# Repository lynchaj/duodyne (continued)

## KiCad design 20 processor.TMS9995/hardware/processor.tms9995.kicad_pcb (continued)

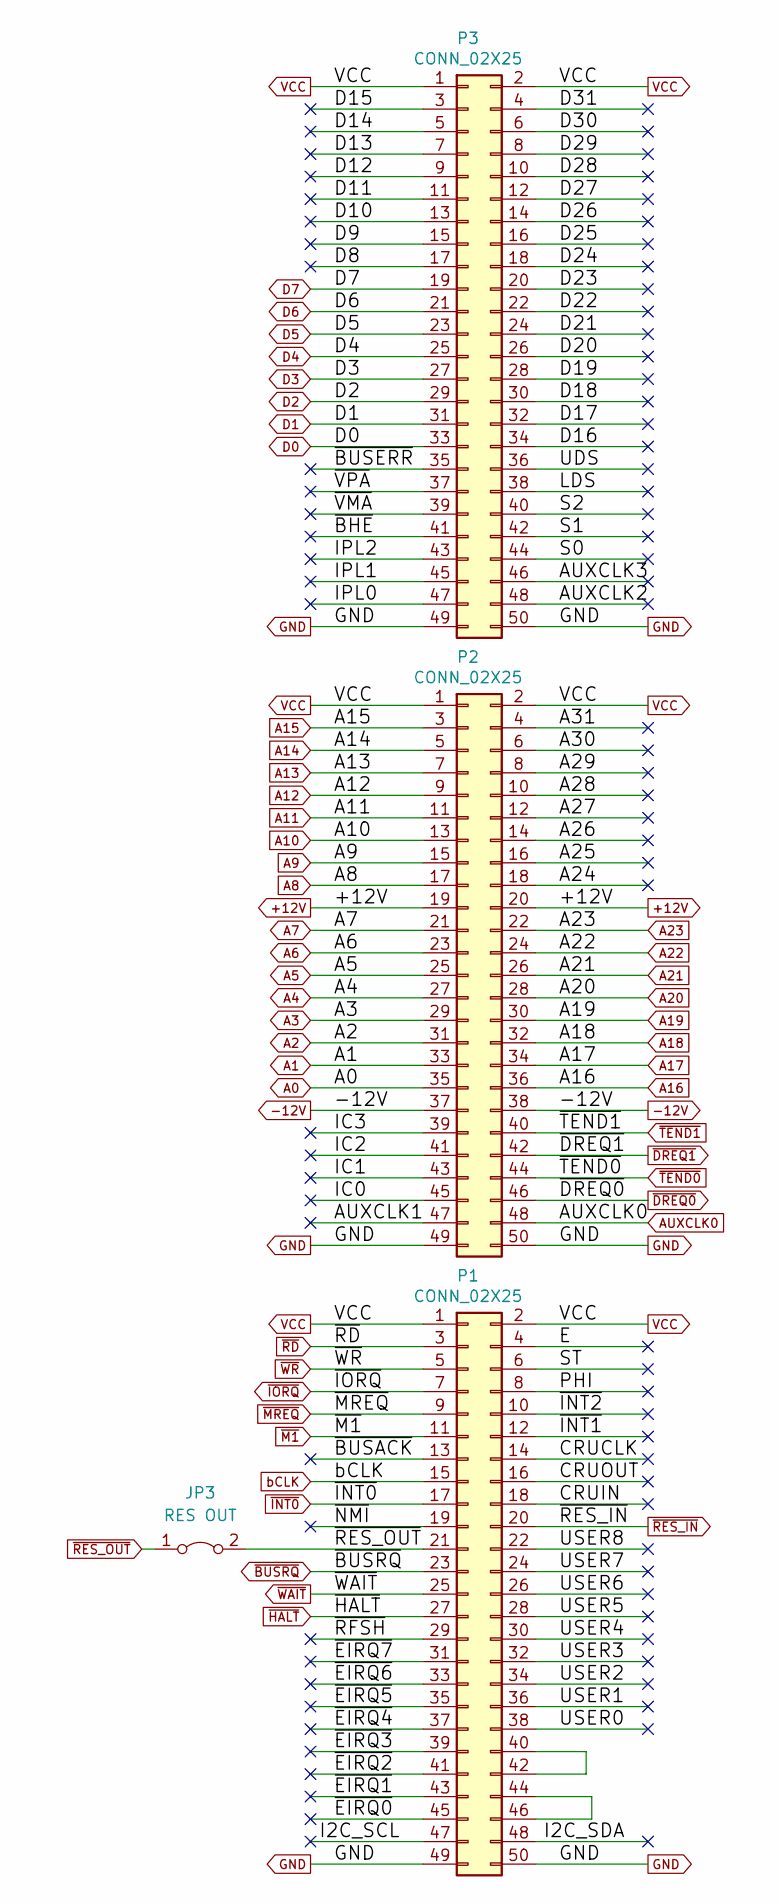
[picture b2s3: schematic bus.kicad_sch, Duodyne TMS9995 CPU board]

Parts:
JP3: RES OUT; SolderJumper-2_P1.3mm_Bridged_Pad1.0x1.5mm
P1, P2, P3: CONN_02X25; IDC-Header_2x25_P2.54mm_Horizontal

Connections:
+12V: P2.19, P2.20
-12V: P2.37, P2.38
/bus/A24: P2.18
/bus/A25: P2.16
/bus/A26: P2.14
/bus/A27: P2.12
/bus/A28: P2.10
/bus/A29: P2.8
/bus/A30: P2.6
/bus/A31: P2.4
/bus/AUXCLK1: P2.47
/bus/AUXCLK2: P3.48
/bus/AUXCLK3: P3.46
/bus/CRUCLK: P1.14
/bus/CRUIN: P1.18
/bus/CRUOUT: P1.16
/bus/D8: P3.17
/bus/D9: P3.15
/bus/D10: P3.13
/bus/D11: P3.11
/bus/D12: P3.9
/bus/D13: P3.7
/bus/D14: P3.5
/bus/D15: P3.3
/bus/D16: P3.34
/bus/D17: P3.32
/bus/D18: P3.30
/bus/D19: P3.28
/bus/D20: P3.26
/bus/D21: P3.24
/bus/D22: P3.22
/bus/D23: P3.20
/bus/D24: P3.18
/bus/D25: P3.16
/bus/D26: P3.14
/bus/D27: P3.12
/bus/D28: P3.10
/bus/D29: P3.8
/bus/D30: P3.6
/bus/D31: P3.4
/bus/E: P1.4
/bus/I2C_SCL: P1.47
/bus/I2C_SDA: P1.48
/bus/IC0: P2.45
/bus/IC1: P2.43
/bus/IC2: P2.41
/bus/IC3: P2.39
/bus/IPL0: P3.47
/bus/IPL1: P3.45
/bus/IPL2: P3.43
/bus/LDS: P3.38
/bus/PHI: P1.8
/bus/S0: P3.44
/bus/S1: P3.42
/bus/S2: P3.40
/bus/ST: P1.6
/bus/UDS: P3.36
/bus/USER0: P1.38
/bus/USER1: P1.36
/bus/USER2: P1.34
/bus/USER3: P1.32
/bus/USER4: P1.30
/bus/USER5: P1.28
/bus/USER6: P1.26
/bus/USER7: P1.24
/bus/USER8: P1.22
/bus/~BHE: P3.41
/bus/~BUSACK: P1.13
/bus/~BUSERR: P3.35
/bus/~EIRQ0: P1.45
/bus/~EIRQ1: P1.43
/bus/~EIRQ2: P1.41
/bus/~EIRQ3: P1.39
/bus/~EIRQ4: P1.37
/bus/~EIRQ5: P1.35
/bus/~EIRQ6: P1.33
/bus/~EIRQ7: P1.31
/bus/~INT1: P1.12
/bus/~INT2: P1.10
/bus/~NMI: P1.19
/bus/~RFSH: P1.29
/bus/~VMA: P3.39
/bus/~VPA: P3.37
A0: P2.35; also elsewhere on the board
A1: P2.33; also elsewhere on the board
A2: P2.31; also elsewhere on the board
A3: P2.29; also elsewhere on the board
A4: P2.27; also elsewhere on the board
A5: P2.25; also elsewhere on the board
A6: P2.23; also elsewhere on the board
A7: P2.21; also elsewhere on the board
A8: P2.17; also elsewhere on the board
A9: P2.15; also elsewhere on the board
A10: P2.13; also elsewhere on the board
A11: P2.11; also elsewhere on the board
A12: P2.9; also elsewhere on the board
A13: P2.7; also elsewhere on the board
A14: P2.5; also elsewhere on the board
A15: P2.3; also elsewhere on the board
A16: P2.36; also elsewhere on the board
A17: P2.34; also elsewhere on the board
A18: P2.32; also elsewhere on the board
A19: P2.30; also elsewhere on the board
A20: P2.28; also elsewhere on the board
A21: P2.26; also elsewhere on the board
A22: P2.24; also elsewhere on the board
A23: P2.22; also elsewhere on the board
AUXCLK0: P2.48; also elsewhere on the board
D0: P3.33; also elsewhere on the board
D1: P3.31; also elsewhere on the board
D2: P3.29; also elsewhere on the board
D3: P3.27; also elsewhere on the board
D4: P3.25; also elsewhere on the board
D5: P3.23; also elsewhere on the board
D6: P3.21; also elsewhere on the board
D7: P3.19; also elsewhere on the board
GND: P1.49, P1.50, P2.49, P2.50, P3.49, P3.50; also elsewhere on the board
unnamed: P1.40, P1.42
unnamed: P1.44, P1.46
VCC: P1.1, P1.2, P2.1, P2.2, P3.1, P3.2; also elsewhere on the board
bCLK: P1.15; also elsewhere on the board
~BUSRQ: P1.23; also elsewhere on the board
~DREQ0: P2.46; also elsewhere on the board
~DREQ1: P2.42; also elsewhere on the board
~HALT: P1.27; also elsewhere on the board
~INT0: P1.17; also elsewhere on the board
~IORQ: P1.7; also elsewhere on the board
~M1: P1.11; also elsewhere on the board
~MREQ: P1.9; also elsewhere on the board
~RD: P1.3; also elsewhere on the board
~RES_IN: P1.20; also elsewhere on the board
~TEND0: P2.44; also elsewhere on the board
~TEND1: P2.40; also elsewhere on the board
~WAIT: P1.25; also elsewhere on the board
~WR: P1.5; also elsewhere on the board

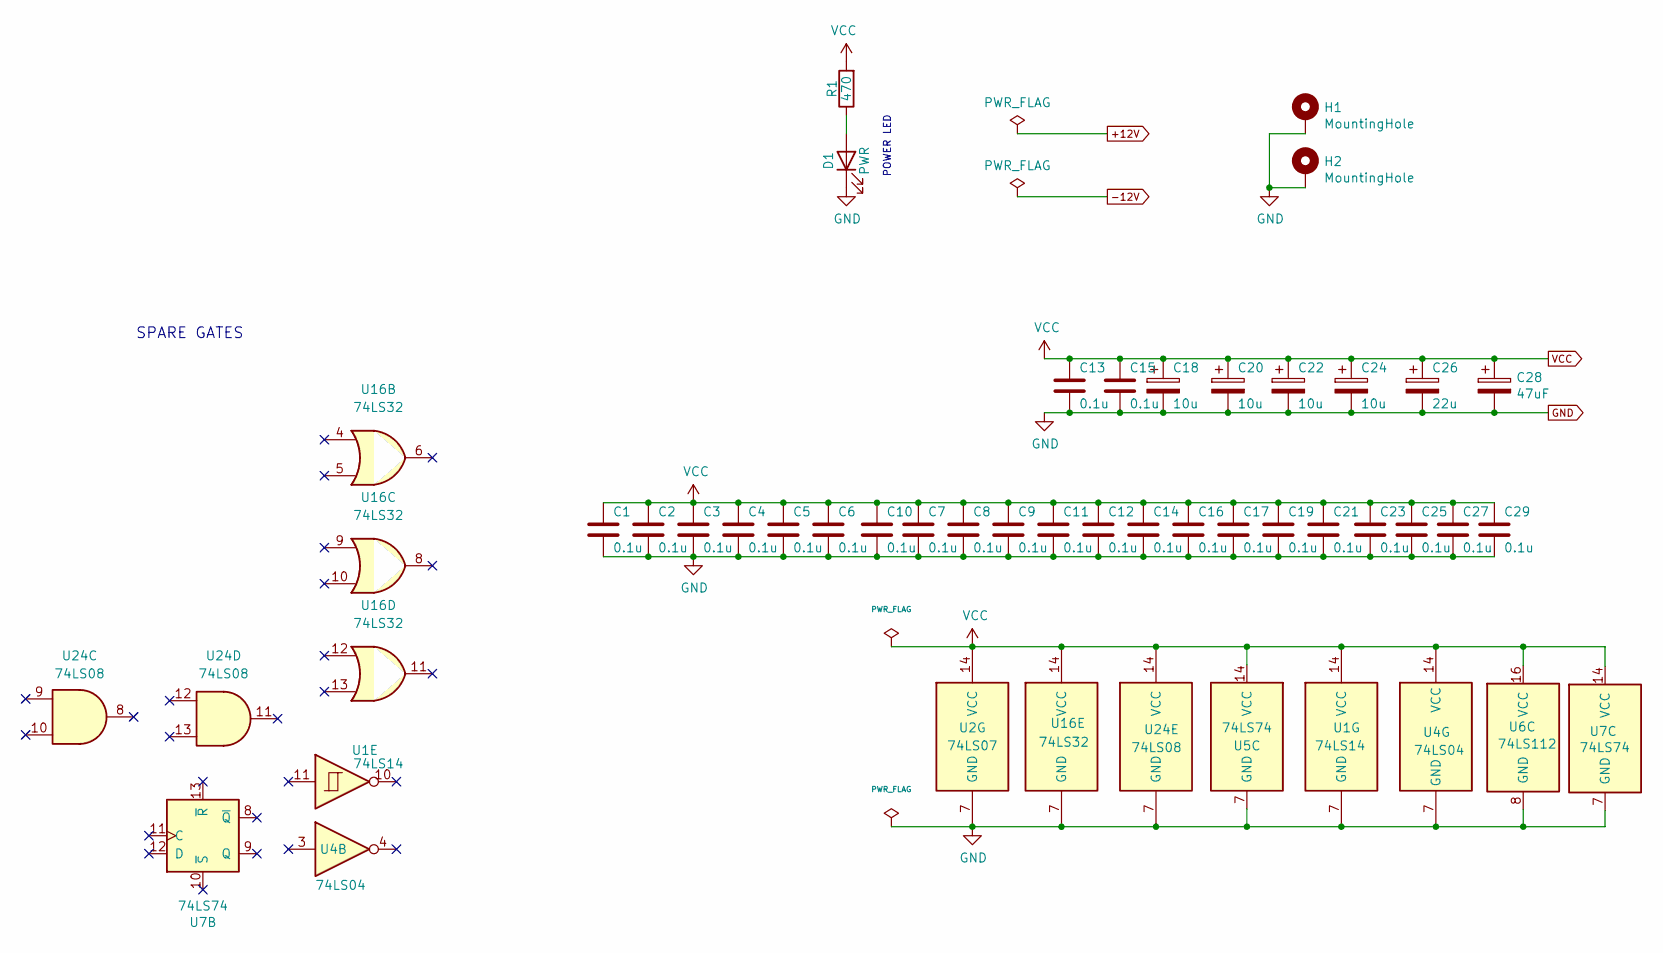
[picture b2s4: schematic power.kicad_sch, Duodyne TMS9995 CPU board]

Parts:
C1, C2, C3, C4, C5, C6, C7, C8, C9, C10, C11, C12, C13, C14, C15, C16, C17, C19, C21, C23, C25, C27, C29: 0.1u; C_Disc_D5.0mm_W2.5mm_P5.00mm
C18, C20, C22, C24: 10u; CP_Radial_D5.0mm_P2.50mm
C26: 22u; CP_Radial_D5.0mm_P2.50mm
C28: 47uF; CP_Radial_D5.0mm_P2.50mm
D1: PWR; LED_D3.0mm_Horizontal_O3.81mm_Z2.0mm
H1, H2: MountingHole; MountingHole_3.2mm_M3_Pad
R1: 470; R_Axial_DIN0207_L6.3mm_D2.5mm_P7.62mm_Horizontal
U1: 74LS14; DIP-14_W7.62mm_Socket_LongPads
U2: 74LS07; DIP-14_W7.62mm_Socket_LongPads
U4: 74LS04; DIP-14_W7.62mm_Socket_LongPads
U5, U7: 74LS74; DIP-14_W7.62mm_Socket_LongPads
U6: 74LS112; DIP-16_W7.62mm_Socket_LongPads
U16: 74LS32; DIP-14_W7.62mm_Socket_LongPads
U24: 74LS08; DIP-14_W7.62mm_Socket_LongPads

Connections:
GND: C1.2, C2.2, C3.2, C4.2, C5.2, C6.2, C7.2, C8.2, C9.2, C10.2, C11.2, C12.2, C13.2, C14.2, C15.2, C16.2, C17.2, C18.2, C19.2, C20.2, C21.2, C22.2, C23.2, C24.2, C25.2, C26.2, C27.2, C28.2, C29.2, D1.1 (K), H1.1, H2.1, U1.7 (GND), U2.7 (GND), U4.7 (GND), U5.7 (GND), U6.8 (GND), U7.7 (GND), U16.7 (GND), U24.7 (GND); also elsewhere on the board
unnamed: D1.2 (A), R1.1
VCC: C1.1, C2.1, C3.1, C4.1, C5.1, C6.1, C7.1, C8.1, C9.1, C10.1, C11.1, C12.1, C13.1, C14.1, C15.1, C16.1, C17.1, C18.1, C19.1, C20.1, C21.1, C22.1, C23.1, C24.1, C25.1, C26.1, C27.1, C28.1, C29.1, R1.2, U1.14 (VCC), U2.14 (VCC), U4.14 (VCC), U5.14 (VCC), U6.16 (VCC), U7.13 (~R), U7.14 (VCC), U16.14 (VCC), U24.14 (VCC); also elsewhere on the board

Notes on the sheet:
POWER LED
SPARE GATES

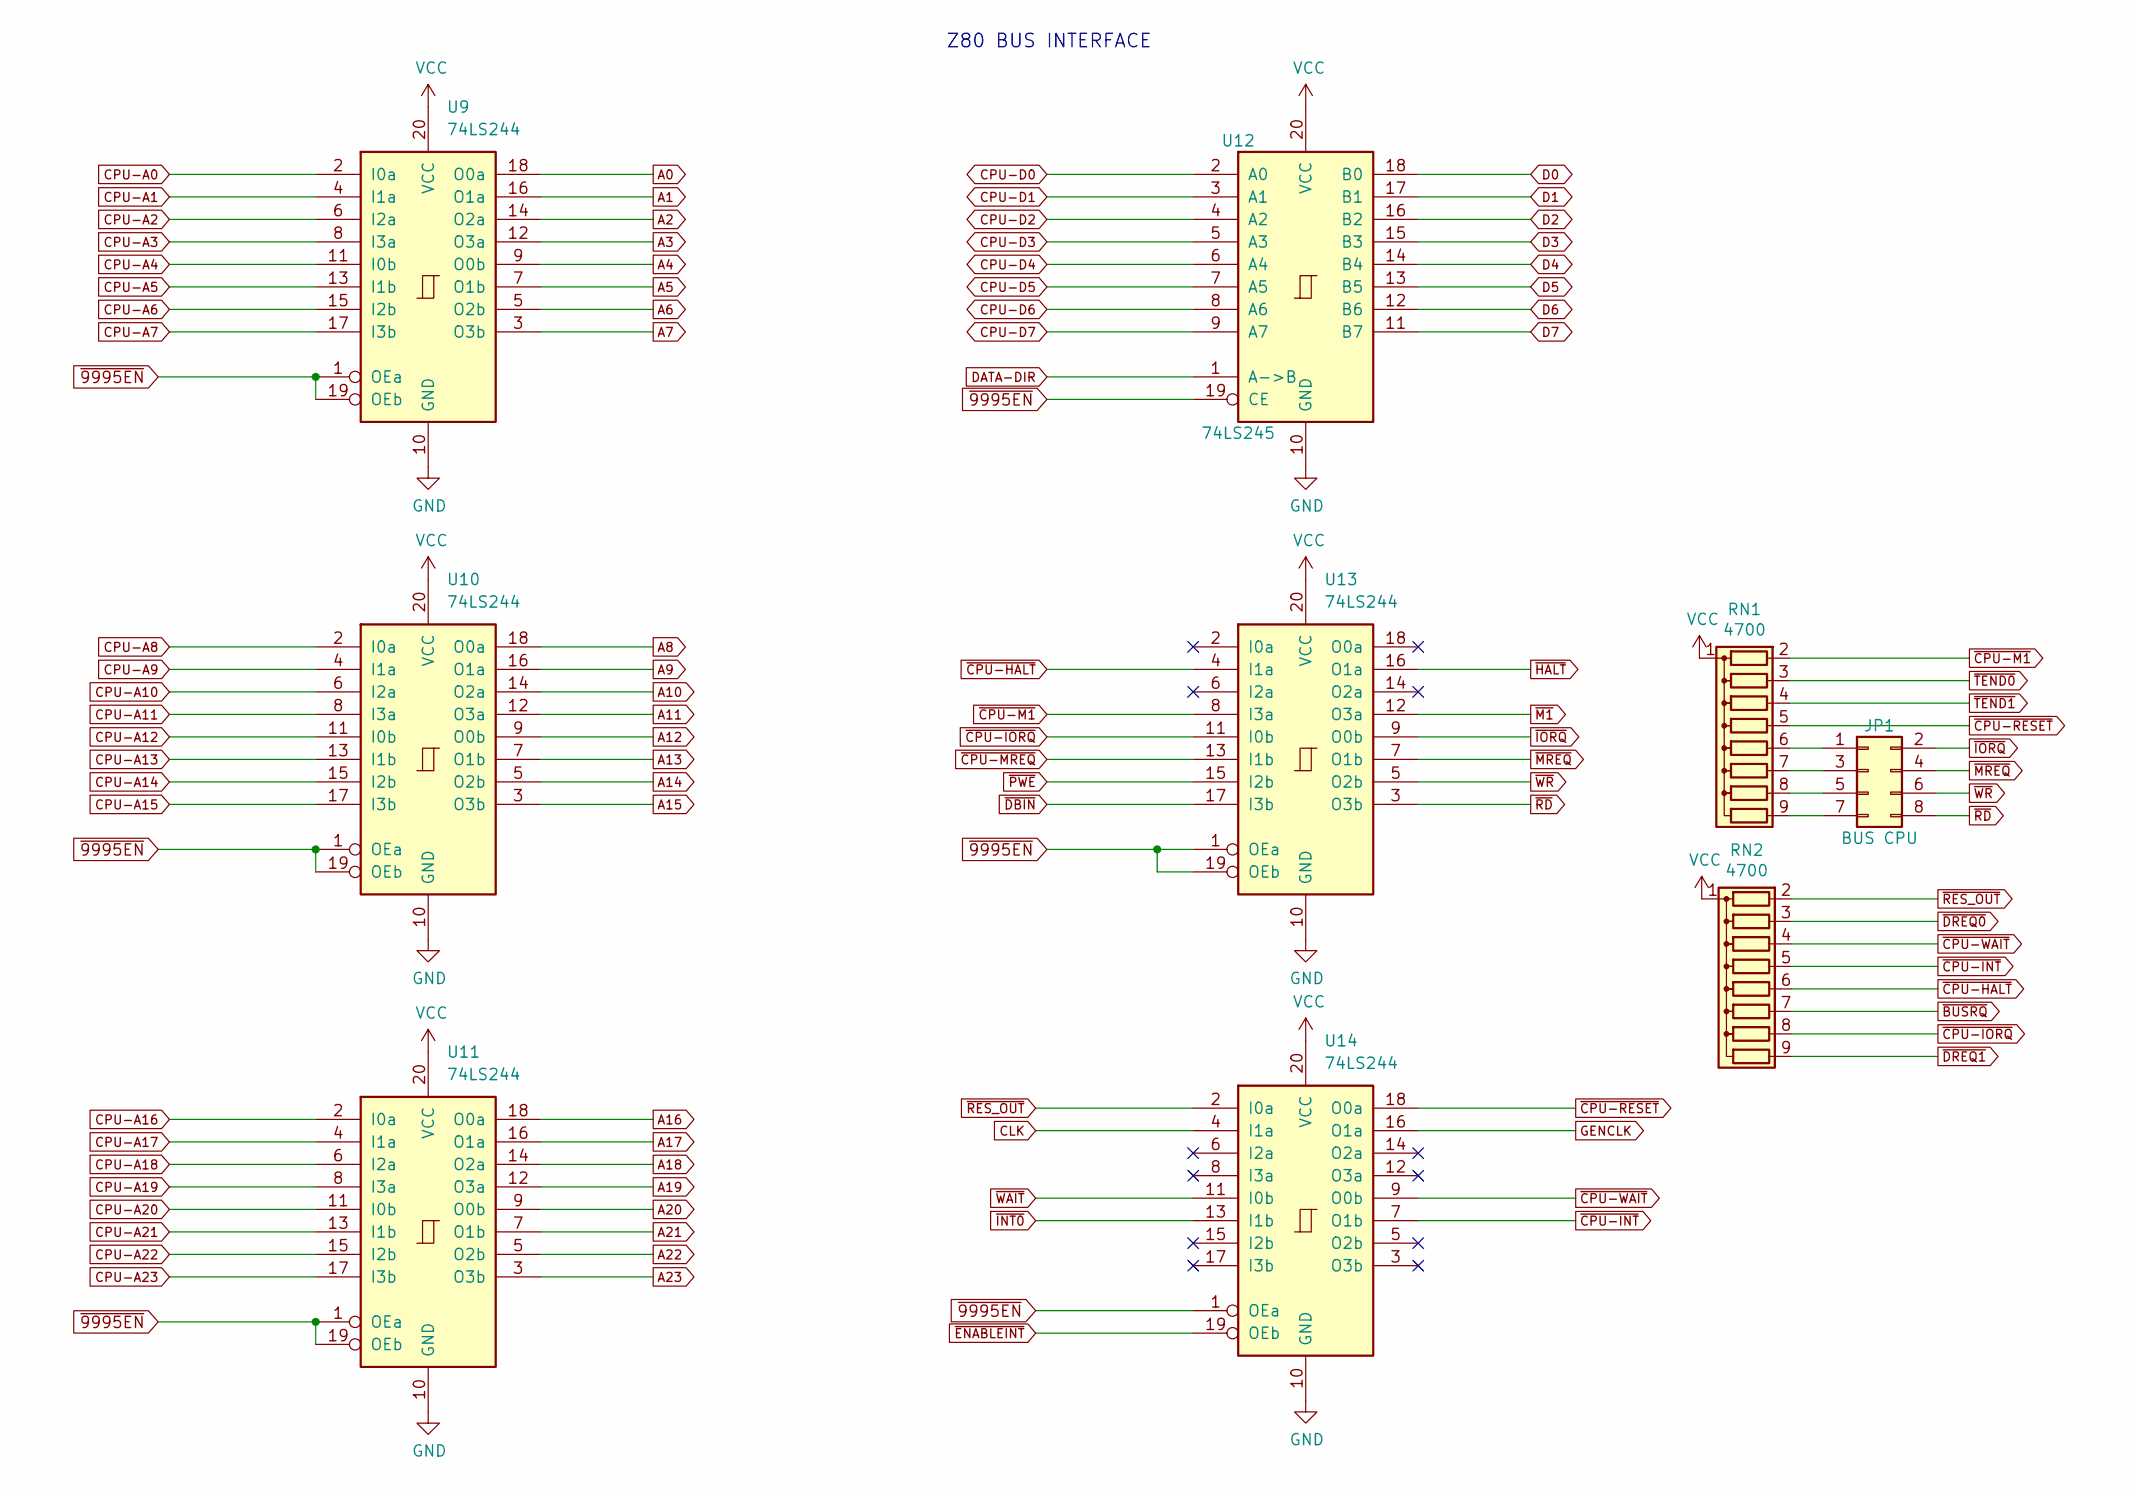
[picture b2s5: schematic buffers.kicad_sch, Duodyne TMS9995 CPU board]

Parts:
JP1: BUS CPU; PinHeader_2x04_P2.54mm_Vertical
RN1, RN2: 4700; R_Array_SIP9
U9, U10, U11, U13, U14: 74LS244; DIP-20_W7.62mm_Socket_LongPads
U12: 74LS245; DIP-20_W7.62mm_Socket_LongPads

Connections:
A0: U9.18 (O0a); also elsewhere on the board
A1: U9.16 (O1a); also elsewhere on the board
A2: U9.14 (O2a); also elsewhere on the board
A3: U9.12 (O3a); also elsewhere on the board
A4: U9.9 (O0b); also elsewhere on the board
A5: U9.7 (O1b); also elsewhere on the board
A6: U9.5 (O2b); also elsewhere on the board
A7: U9.3 (O3b); also elsewhere on the board
A8: U10.18 (O0a); also elsewhere on the board
A9: U10.16 (O1a); also elsewhere on the board
A10: U10.14 (O2a); also elsewhere on the board
A11: U10.12 (O3a); also elsewhere on the board
A12: U10.9 (O0b); also elsewhere on the board
A13: U10.7 (O1b); also elsewhere on the board
A14: U10.5 (O2b); also elsewhere on the board
A15: U10.3 (O3b); also elsewhere on the board
A16: U11.18 (O0a); also elsewhere on the board
A17: U11.16 (O1a); also elsewhere on the board
A18: U11.14 (O2a); also elsewhere on the board
A19: U11.12 (O3a); also elsewhere on the board
A20: U11.9 (O0b); also elsewhere on the board
A21: U11.7 (O1b); also elsewhere on the board
A22: U11.5 (O2b); also elsewhere on the board
A23: U11.3 (O3b); also elsewhere on the board
CLK: U14.4 (I1a); also elsewhere on the board
CPU-A0: U9.2 (I0a); also elsewhere on the board
CPU-A1: U9.4 (I1a); also elsewhere on the board
CPU-A2: U9.6 (I2a); also elsewhere on the board
CPU-A3: U9.8 (I3a); also elsewhere on the board
CPU-A4: U9.11 (I0b); also elsewhere on the board
CPU-A5: U9.13 (I1b); also elsewhere on the board
CPU-A6: U9.15 (I2b); also elsewhere on the board
CPU-A7: U9.17 (I3b); also elsewhere on the board
CPU-A8: U10.2 (I0a); also elsewhere on the board
CPU-A9: U10.4 (I1a); also elsewhere on the board
CPU-A10: U10.6 (I2a); also elsewhere on the board
CPU-A11: U10.8 (I3a); also elsewhere on the board
CPU-A12: U10.11 (I0b); also elsewhere on the board
CPU-A13: U10.13 (I1b); also elsewhere on the board
CPU-A14: U10.15 (I2b); also elsewhere on the board
CPU-A15: U10.17 (I3b); also elsewhere on the board
CPU-A16: U11.2 (I0a); also elsewhere on the board
CPU-A17: U11.4 (I1a); also elsewhere on the board
CPU-A18: U11.6 (I2a); also elsewhere on the board
CPU-A19: U11.8 (I3a); also elsewhere on the board
CPU-A20: U11.11 (I0b); also elsewhere on the board
CPU-A21: U11.13 (I1b); also elsewhere on the board
CPU-A22: U11.15 (I2b); also elsewhere on the board
CPU-A23: U11.17 (I3b); also elsewhere on the board
CPU-D0: U12.2 (A0); also elsewhere on the board
CPU-D1: U12.3 (A1); also elsewhere on the board
CPU-D2: U12.4 (A2); also elsewhere on the board
CPU-D3: U12.5 (A3); also elsewhere on the board
CPU-D4: U12.6 (A4); also elsewhere on the board
CPU-D5: U12.7 (A5); also elsewhere on the board
CPU-D6: U12.8 (A6); also elsewhere on the board
CPU-D7: U12.9 (A7); also elsewhere on the board
D0: U12.18 (B0); also elsewhere on the board
D1: U12.17 (B1); also elsewhere on the board
D2: U12.16 (B2); also elsewhere on the board
D3: U12.15 (B3); also elsewhere on the board
D4: U12.14 (B4); also elsewhere on the board
D5: U12.13 (B5); also elsewhere on the board
D6: U12.12 (B6); also elsewhere on the board
D7: U12.11 (B7); also elsewhere on the board
DATA-DIR: U12.1 (A->B); also elsewhere on the board
GENCLK: U14.16 (O1a); also elsewhere on the board
GND: U9.10 (GND), U10.10 (GND), U11.10 (GND), U12.10 (GND), U13.10 (GND), U14.10 (GND); also elsewhere on the board
unnamed: JP1.1, RN1.6 (R5)
unnamed: JP1.3, RN1.7 (R6)
unnamed: JP1.5, RN1.8 (R7)
unnamed: JP1.7, RN1.9 (R8)
VCC: RN1.1 (common), RN2.1 (common), U9.20 (VCC), U10.20 (VCC), U11.20 (VCC), U12.20 (VCC), U13.20 (VCC), U14.20 (VCC); also elsewhere on the board
~9995EN: U9.1 (OEa), U9.19 (OEb), U10.1 (OEa), U10.19 (OEb), U11.1 (OEa), U11.19 (OEb), U12.19 (CE), U13.1 (OEa), U13.19 (OEb), U14.1 (OEa); also elsewhere on the board
~BUSRQ: RN2.7 (R6); also elsewhere on the board
~CPU-HALT: RN2.6 (R5), U13.4 (I1a)
~CPU-INT: RN2.5 (R4), U14.7 (O1b); also elsewhere on the board
~CPU-IORQ: RN2.8 (R7), U13.11 (I0b); also elsewhere on the board
~CPU-M1: RN1.2 (R1), U13.8 (I3a)
~CPU-MREQ: U13.13 (I1b); also elsewhere on the board
~CPU-RESET: RN1.5 (R4), U14.18 (O0a)
~CPU-WAIT: RN2.4 (R3), U14.9 (O0b); also elsewhere on the board
~DBIN: U13.17 (I3b); also elsewhere on the board
~DREQ0: RN2.3 (R2); also elsewhere on the board
~DREQ1: RN2.9 (R8); also elsewhere on the board
~ENABLEINT: U14.19 (OEb); also elsewhere on the board
~HALT: U13.16 (O1a); also elsewhere on the board
~INT0: U14.13 (I1b); also elsewhere on the board
~IORQ: JP1.2, U13.9 (O0b); also elsewhere on the board
~M1: U13.12 (O3a); also elsewhere on the board
~MREQ: JP1.4, U13.7 (O1b); also elsewhere on the board
~PWE: U13.15 (I2b); also elsewhere on the board
~RD: JP1.8, U13.3 (O3b); also elsewhere on the board
~TEND0: RN1.3 (R2); also elsewhere on the board
~TEND1: RN1.4 (R3); also elsewhere on the board
~WAIT: U14.11 (I0b); also elsewhere on the board
~WR: JP1.6, U13.5 (O2b); also elsewhere on the board

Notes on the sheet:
Z80 BUS INTERFACE

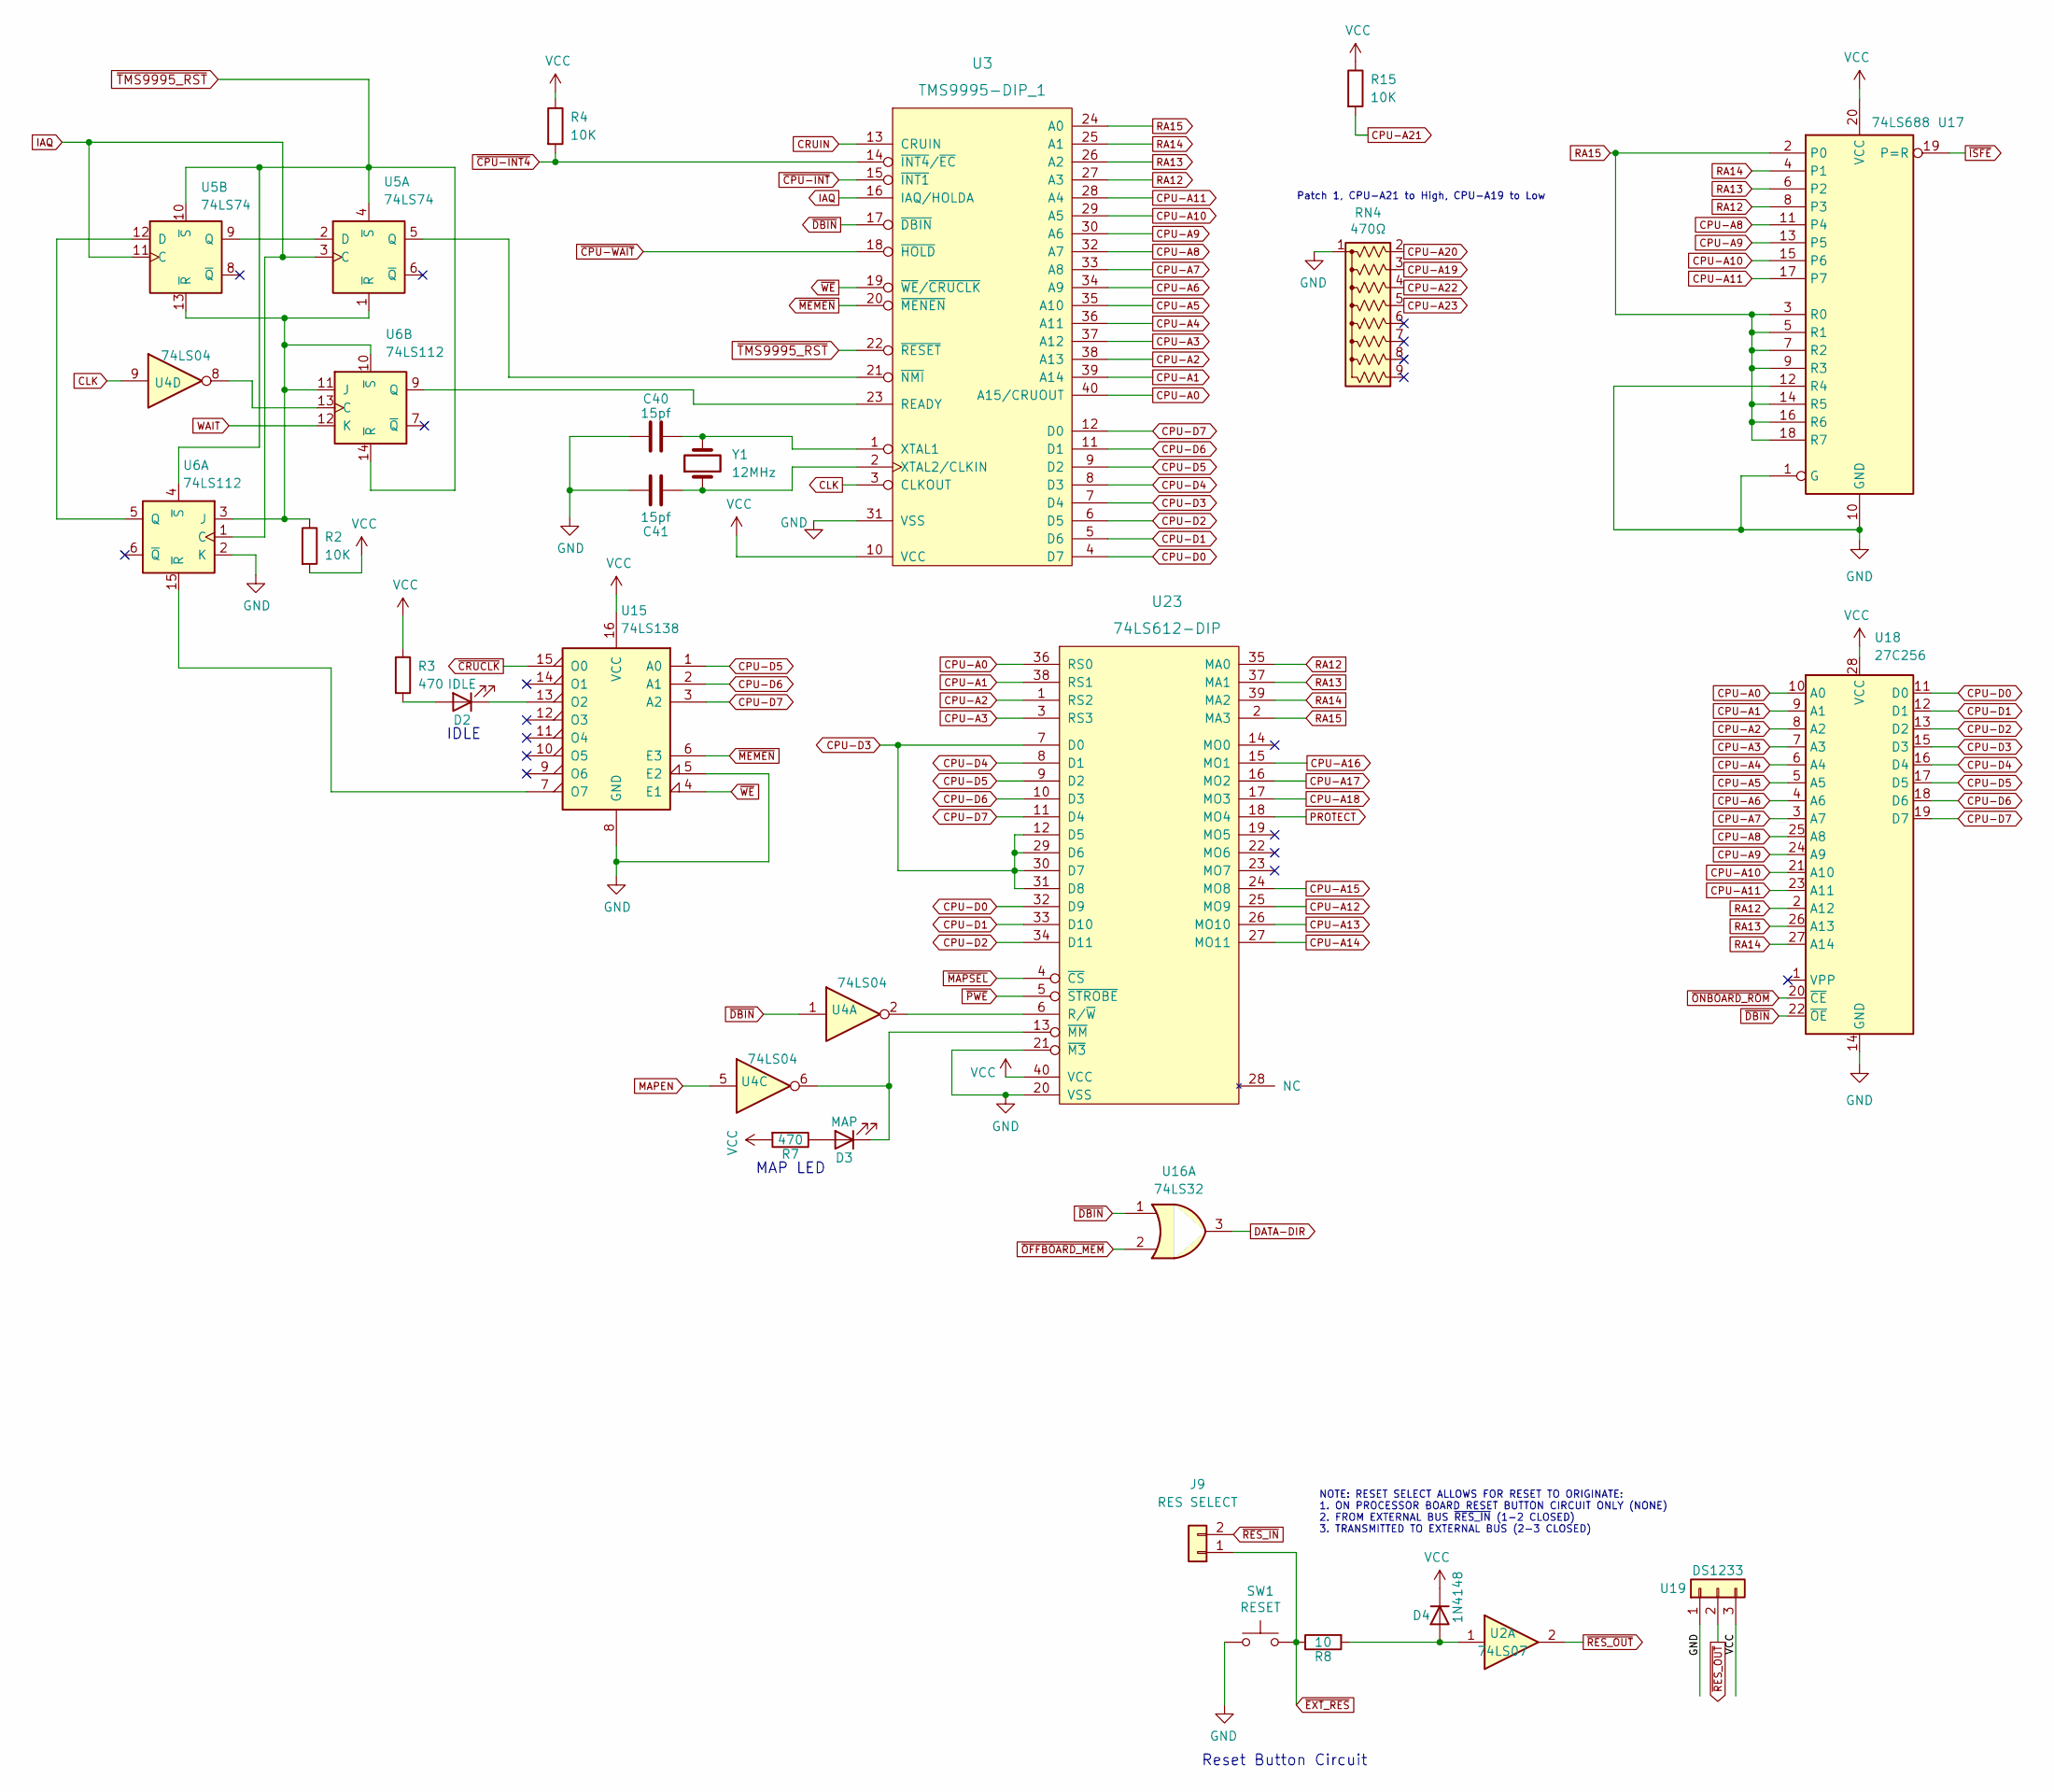
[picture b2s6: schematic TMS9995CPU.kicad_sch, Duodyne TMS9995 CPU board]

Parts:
C40, C41: 15pf; C_Disc_D5.0mm_W2.5mm_P5.00mm
D2: IDLE; LED_D3.0mm_Horizontal_O3.81mm_Z2.0mm
D3: MAP; LED_D3.0mm_Horizontal_O3.81mm_Z2.0mm
D4: 1N4148; D_DO-35_SOD27_P7.62mm_Horizontal
J9: RES SELECT; PinHeader_1x02_P2.54mm_Vertical
R2, R4, R15: 10K; R_Axial_DIN0207_L6.3mm_D2.5mm_P7.62mm_Horizontal
R3, R7: 470; R_Axial_DIN0207_L6.3mm_D2.5mm_P7.62mm_Horizontal
R8: 10; R_Axial_DIN0207_L6.3mm_D2.5mm_P7.62mm_Horizontal
RN4: 470Ω; R_Array_SIP9
SW1: RESET; SW_Tactile_SPST_Angled_PTS645Vx58-2LFS
U2: 74LS07; DIP-14_W7.62mm_Socket_LongPads
U3: TMS9995-DIP_1; DIP-40_W15.24mm_Socket_LongPads
U4: 74LS04; DIP-14_W7.62mm_Socket_LongPads
U5: 74LS74; DIP-14_W7.62mm_Socket_LongPads
U6: 74LS112; DIP-16_W7.62mm_Socket_LongPads
U15: 74LS138; DIP-16_W7.62mm_Socket_LongPads
U16: 74LS32; DIP-14_W7.62mm_Socket_LongPads
U17: 74LS688; DIP-20_W7.62mm_Socket_LongPads
U18: 27C256; DIP-28_W15.24mm_Socket_LongPads
U19: DS1233; TO-92L_HandSolder
U23: 74LS612-DIP; DIP-40_W15.24mm_Socket_LongPads
Y1: 12MHz; Crystal_HC49-U_Vertical

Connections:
CLK: U3.3 (CLKOUT), U4.9; also elsewhere on the board
CPU-A0: U3.40 (A15/CRUOUT), U18.10 (A0), U23.36 (RS0); also elsewhere on the board
CPU-A1: U3.39 (A14), U18.9 (A1), U23.38 (RS1); also elsewhere on the board
CPU-A2: U3.38 (A13), U18.8 (A2), U23.1 (RS2); also elsewhere on the board
CPU-A3: U3.37 (A12), U18.7 (A3), U23.3 (RS3); also elsewhere on the board
CPU-A4: U3.36 (A11), U18.6 (A4); also elsewhere on the board
CPU-A5: U3.35 (A10), U18.5 (A5); also elsewhere on the board
CPU-A6: U3.34 (A9), U18.4 (A6); also elsewhere on the board
CPU-A7: U3.33 (A8), U18.3 (A7); also elsewhere on the board
CPU-A8: U3.32 (A7), U17.11 (P4), U18.25 (A8); also elsewhere on the board
CPU-A9: U3.30 (A6), U17.13 (P5), U18.24 (A9); also elsewhere on the board
CPU-A10: U3.29 (A5), U17.15 (P6), U18.21 (A10); also elsewhere on the board
CPU-A11: U3.28 (A4), U17.17 (P7), U18.23 (A11); also elsewhere on the board
CPU-A12: U23.25 (MO9); also elsewhere on the board
CPU-A13: U23.26 (MO10); also elsewhere on the board
CPU-A14: U23.27 (MO11); also elsewhere on the board
CPU-A15: U23.24 (MO8); also elsewhere on the board
CPU-A16: U23.15 (MO1); also elsewhere on the board
CPU-A17: U23.16 (MO2); also elsewhere on the board
CPU-A18: U23.17 (MO3); also elsewhere on the board
CPU-A19: RN4.3 (R2); also elsewhere on the board
CPU-A20: RN4.2 (R1); also elsewhere on the board
CPU-A21: R15.2; also elsewhere on the board
CPU-A22: RN4.4 (R3); also elsewhere on the board
CPU-A23: RN4.5 (R4); also elsewhere on the board
CPU-D0: U3.4 (D7), U18.11 (D0), U23.32 (D9); also elsewhere on the board
CPU-D1: U3.5 (D6), U18.12 (D1), U23.33 (D10); also elsewhere on the board
CPU-D2: U3.6 (D5), U18.13 (D2), U23.34 (D11); also elsewhere on the board
CPU-D3: U3.7 (D4), U18.15 (D3), U23.7 (D0), U23.12 (D5), U23.29 (D6), U23.30 (D7), U23.31 (D8); also elsewhere on the board
CPU-D4: U3.8 (D3), U18.16 (D4), U23.8 (D1); also elsewhere on the board
CPU-D5: U3.9 (D2), U15.1 (A0), U18.17 (D5), U23.9 (D2); also elsewhere on the board
CPU-D6: U3.11 (D1), U15.2 (A1), U18.18 (D6), U23.10 (D3); also elsewhere on the board
CPU-D7: U3.12 (D0), U15.3 (A2), U18.19 (D7), U23.11 (D4); also elsewhere on the board
CRUIN: U3.13 (CRUIN); also elsewhere on the board
DATA-DIR: U16.3; also elsewhere on the board
GND: C40.1, C41.1, RN4.1 (common), SW1.2, U3.31 (VSS), U6.2 (K), U15.5 (E2), U15.8 (GND), U17.1 (G), U17.10 (GND), U17.12 (R4), U18.14 (GND), U19.1, U23.20 (VSS), U23.21 (~M3); also elsewhere on the board
IAQ: U3.16 (IAQ/HOLDA), U5.3 (C), U5.11 (C), U6.1 (C)
MAPEN: U4.5; also elsewhere on the board
unnamed: C40.2, U3.1 (XTAL1), Y1.2
unnamed: C41.2, U3.2 (XTAL2/CLKIN), Y1.1
unnamed: D2.1 (K), U15.13 (O2)
unnamed: D2.2 (A), R3.2
unnamed: D3.1 (K), U4.6, U23.13 (~MM)
unnamed: D3.2 (A), R7.1
unnamed: D4.2 (A), R8.2, U2.1
unnamed: R2.1, U5.1 (~R), U5.13 (~R), U6.3 (J), U6.10 (~S), U6.11 (J)
unnamed: U3.21 (~NMI), U5.5 (Q)
unnamed: U3.23 (READY), U6.9 (Q)
unnamed: U4.8, U6.13 (C)
unnamed: U5.2 (D), U5.9 (Q)
unnamed: U5.12 (D), U6.5 (Q)
unnamed: U6.15 (~R), U15.7 (O7)
unnamed: U4.2, U23.6 (R/~W)
PROTECT: U23.18 (MO4); also elsewhere on the board
RA12: U3.27 (A3), U17.8 (P3), U18.2 (A12), U23.35 (MA0)
RA13: U3.26 (A2), U17.6 (P2), U18.26 (A13), U23.37 (MA1)
RA14: U3.25 (A1), U17.4 (P1), U18.27 (A14), U23.39 (MA2)
RA15: U3.24 (A0), U17.2 (P0), U17.3 (R0), U17.5 (R1), U17.7 (R2), U17.9 (R3), U17.14 (R5), U17.16 (R6), U17.18 (R7), U23.2 (MA3); also elsewhere on the board
VCC: D4.1 (K), R2.2, R3.1, R4.1, R7.2, R15.1, U3.10 (VCC), U15.16 (VCC), U17.20 (VCC), U18.28 (VCC), U19.3, U23.40 (VCC); also elsewhere on the board
WAIT: U6.12 (K); also elsewhere on the board
~CPU-INT4: R4.2, U3.14 (~INT4/~EC); also elsewhere on the board
~CPU-INT: U3.15 (~INT1); also elsewhere on the board
~CPU-WAIT: U3.18 (~HOLD); also elsewhere on the board
~CRUCLK: U15.15 (O0); also elsewhere on the board
~DBIN: U3.17 (~DBIN), U4.1, U16.1, U18.22 (~OE); also elsewhere on the board
~EXT_RES: J9.1, R8.1, SW1.1
~ISFE: U17.19 (P=R); also elsewhere on the board
~MAPSEL: U23.4 (~CS); also elsewhere on the board
~MEMEN: U3.20 (~MENEN), U15.6 (E3); also elsewhere on the board
~OFFBOARD_MEM: U16.2; also elsewhere on the board
~ONBOARD_ROM: U18.20 (~CE); also elsewhere on the board
~PWE: U23.5 (~STROBE); also elsewhere on the board
~RES_IN: J9.2; also elsewhere on the board
~TMS9995_RST: U3.22 (~RESET), U5.4 (~S), U5.10 (~S), U6.4 (~S), U6.14 (~R); also elsewhere on the board
~WE: U3.19 (~WE/~CRUCLK), U15.4 (E1); also elsewhere on the board

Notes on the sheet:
Patch 1, CPU-A21 to High, CPU-A19 to Low
Reset Button Circuit
MAP LED
IDLE
NOTE: RESET SELECT ALLOWS FOR RESET TO ORIGINATE: 1. ON PROCESSOR BOARD RESET BUTTON CIRCUIT ONLY (NONE) 2. FROM EXTERNAL BUS ~{RES_IN} (1-2 CLOSED) 3. TRANSMITTED TO EXTERNAL BUS (2-3 CLOSED)

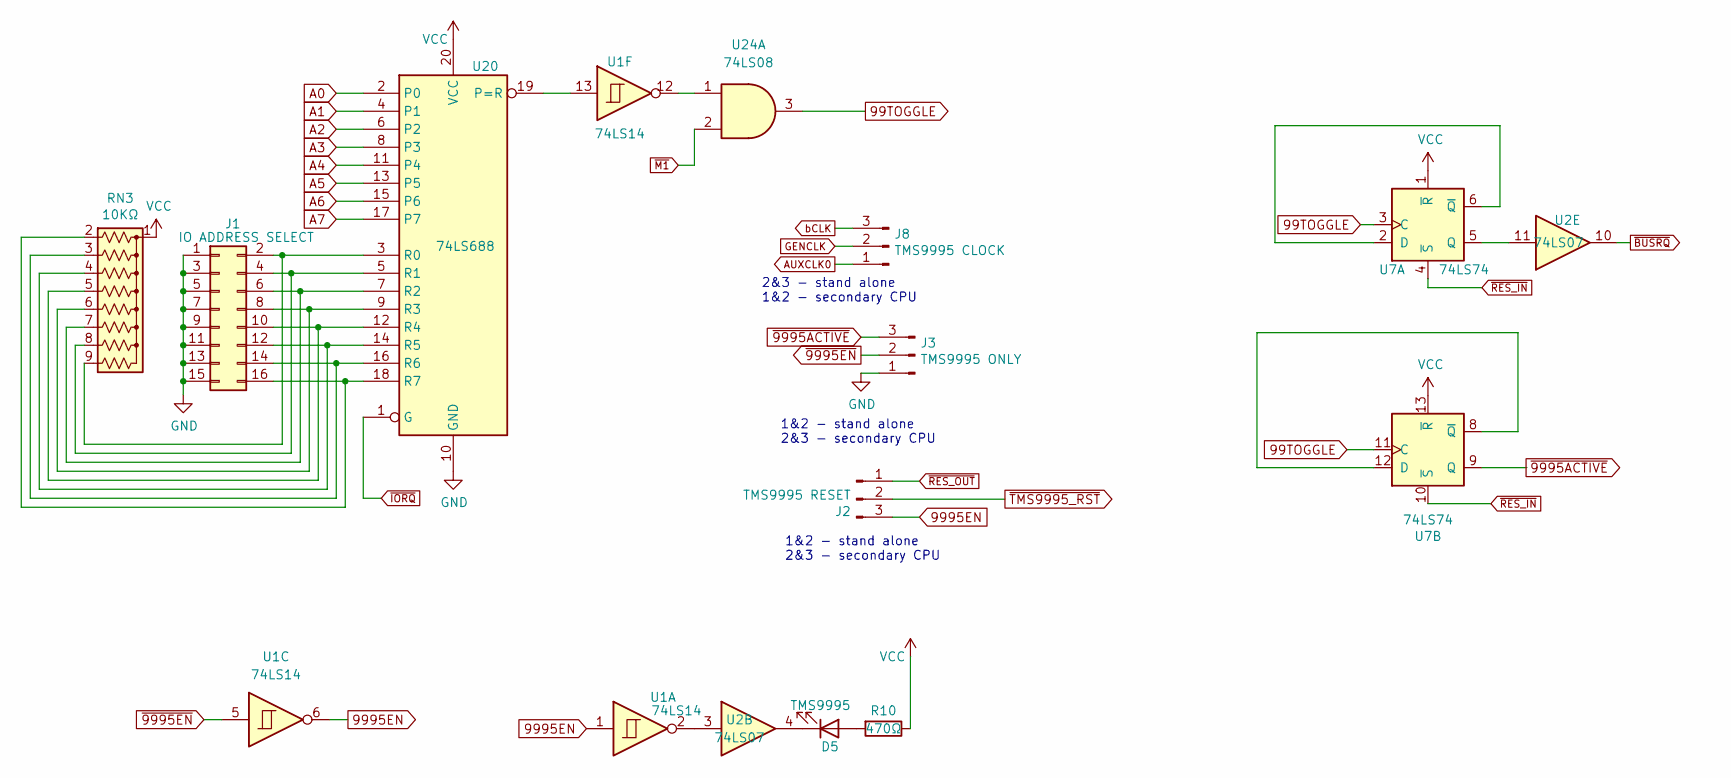
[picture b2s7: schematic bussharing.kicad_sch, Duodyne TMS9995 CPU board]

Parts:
D5: TMS9995; LED_D3.0mm_Horizontal_O3.81mm_Z2.0mm
J1: IO ADDRESS SELECT; PinHeader_2x08_P2.54mm_Vertical
J2: TMS9995 RESET; PinHeader_1x03_P2.54mm_Horizontal
J3: TMS9995 ONLY; PinHeader_1x03_P2.54mm_Horizontal
J8: TMS9995 CLOCK; PinHeader_1x03_P2.54mm_Horizontal
R10: 470Ω; R_Axial_DIN0207_L6.3mm_D2.5mm_P7.62mm_Horizontal
RN3: 10KΩ; R_Array_SIP9
U1: 74LS14; DIP-14_W7.62mm_Socket_LongPads
U2: 74LS07; DIP-14_W7.62mm_Socket_LongPads
U7: 74LS74; DIP-14_W7.62mm_Socket_LongPads
U20: 74LS688; DIP-20_W7.62mm_Socket_LongPads
U24: 74LS08; DIP-14_W7.62mm_Socket_LongPads

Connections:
9995EN: J2.3, U1.1, U1.6
A0: U20.2 (P0); also elsewhere on the board
A1: U20.4 (P1); also elsewhere on the board
A2: U20.6 (P2); also elsewhere on the board
A3: U20.8 (P3); also elsewhere on the board
A4: U20.11 (P4); also elsewhere on the board
A5: U20.13 (P5); also elsewhere on the board
A6: U20.15 (P6); also elsewhere on the board
A7: U20.17 (P7); also elsewhere on the board
AUXCLK0: J8.1; also elsewhere on the board
GENCLK: J8.2; also elsewhere on the board
GND: J1.1, J1.3, J1.5, J1.7, J1.9, J1.11, J1.13, J1.15, J3.1, U20.10 (GND); also elsewhere on the board
unnamed: D5.1 (K), U2.4
unnamed: D5.2 (A), R10.2
unnamed: J1.2, RN3.9 (R8), U20.3 (R0)
unnamed: J1.4, RN3.8 (R7), U20.5 (R1)
unnamed: J1.6, RN3.7 (R6), U20.7 (R2)
unnamed: J1.8, RN3.6 (R5), U20.9 (R3)
unnamed: J1.10, RN3.5 (R4), U20.12 (R4)
unnamed: J1.12, RN3.4 (R3), U20.14 (R5)
unnamed: J1.14, RN3.3 (R2), U20.16 (R6)
unnamed: J1.16, RN3.2 (R1), U20.18 (R7)
unnamed: U1.2, U2.3
unnamed: U1.13, U20.19 (P=R)
unnamed 203: U7.2 (D), U7.6 (~Q); also elsewhere on the board
VCC: R10.1, RN3.1 (common), U7.1 (~R), U7.13 (~R), U20.20 (VCC); also elsewhere on the board
bCLK: J8.3; also elsewhere on the board
~9995EN: J3.2, U1.5; also elsewhere on the board
~BUSRQ: U2.10; also elsewhere on the board
~IORQ: U20.1 (G); also elsewhere on the board
~TMS9995_RST: J2.2; also elsewhere on the board

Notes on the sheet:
1&2 - stand alone 2&3 - secondary CPU
2&3 - stand alone 1&2 - secondary CPU

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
